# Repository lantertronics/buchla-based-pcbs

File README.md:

# buchla-based-pcbs

291

294

295

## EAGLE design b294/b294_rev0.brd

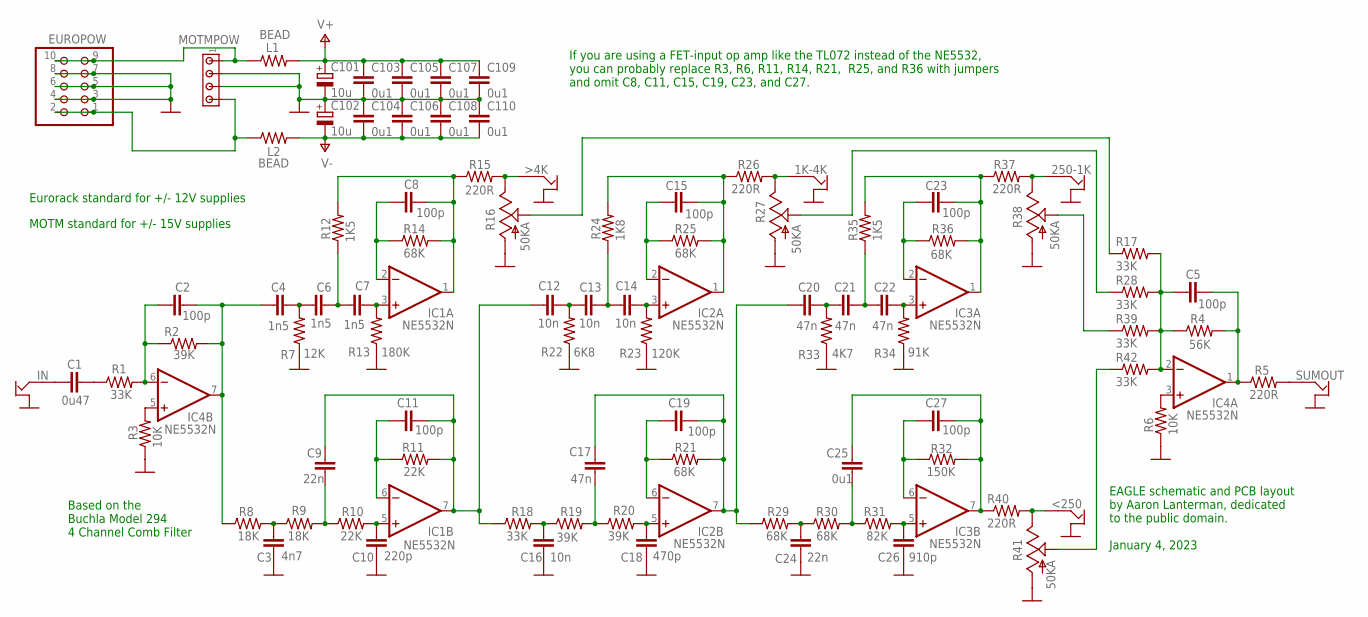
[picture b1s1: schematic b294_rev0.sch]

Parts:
1K-4K, 250-1K: OFFBOARD2JACKALT_AARON; OFFBOARD2JACKALT
<250: OFFBOARD2JACKALT_AARON; OFFBOARD2JACKALT
>4K: OFFBOARD2JACKALT_AARON; OFFBOARD2JACKALT
C1: 0u47; C050-025X075
C2, C5, C8, C11, C15, C19, C23, C27: 100p; C050-025X075
C3: 4n7; C050-025X075
C4, C6, C7: 1n5; C050-025X075
C9, C24: 22n; C050-025X075
C10: 220p; C050-025X075
C12, C13, C14, C16: 10n; C050-025X075
C17, C20, C21, C22: 47n; C050-025X075
C18: 470p; C050-025X075
C25, C103, C104, C105, C106, C107, C108, C109, C110: 0u1; C050-025X075
C26: 910p; C050-025X075
C101, C102: 10u; E1,8-4
EUROPOW: PINHD-2X5; 2X05
IC1, IC2, IC3, IC4: NE5532N; DIL08
IN: OFFBOARD2JACKALT_AARON; OFFBOARD2JACKALT
L1, L2: BEAD; 0207/10
MOTMPOW: MTA04-156; 1X4MTA
R1, R17, R18, R28, R39, R42: 33K; 0207/10
R2, R19, R20: 39K; 0207/10
R3, R6: 10K; 0207/10
R4: 56K; 0207/10
R5, R15, R26, R37, R40: 220R; 0207/10
R7: 12K; 0207/10
R8, R9: 18K; 0207/10
R10, R11: 22K; 0207/10
R12, R35: 1K5; 0207/10
R13: 180K; 0207/10
R14, R21, R25, R29, R30, R36: 68K; 0207/10
R16, R27, R38, R41: 50KA; B64Y
R22: 6K8; 0207/10
R23: 120K; 0207/10
R24: 1K8; 0207/10
R31: 82K; 0207/10
R32: 150K; 0207/10
R33: 4K7; 0207/10
R34: 91K; 0207/10
SUMOUT: OFFBOARD2JACKALT_AARON; OFFBOARD2JACKALT

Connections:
GND: 1K-4K.GND, 250-1K.GND, <250.GND, >4K.GND, C3.2, C10.2, C16.2, C18.2, C24.2, C26.2, C101.-, C102.+, C103.2, C104.1, C105.2, C106.1, C107.2, C108.1, C109.2, C110.1, EUROPOW.3, EUROPOW.4, EUROPOW.5, EUROPOW.6, EUROPOW.7, EUROPOW.8, IN.GND, MOTMPOW.2, MOTMPOW.3, R3.1, R6.1, R7.1, R13.1, R16.A, R22.1, R23.1, R27.A, R33.1, R34.1, R38.A, R41.A, SUMOUT.GND
unnamed: C18.1, IC2.5 (+IN), R20.2
unnamed: C17.2, R19.2, R20.1
unnamed: C16.1, R18.2, R19.1
unnamed: C26.1, IC3.5 (+IN), R31.2
unnamed: C25.2, R30.2, R31.1
unnamed: C24.1, R29.2, R30.1
unnamed: C10.1, IC1.5 (+IN), R10.2
unnamed: >4K.SIGNAL, R15.2, R16.E
unnamed: C3.1, R8.2, R9.1
unnamed: C11.1, IC1.6 (-IN), R11.1
unnamed: C9.1, C11.2, C12.1, IC1.7 (OUT), R11.2, R18.1
unnamed: C19.1, IC2.6 (-IN), R21.1
unnamed: C17.1, C19.2, C20.1, IC2.7 (OUT), R21.2, R29.1
unnamed: C2.2, C4.1, IC4.7 (OUT), R2.2, R8.1
unnamed: C25.1, C27.2, IC3.7 (OUT), R32.2, R40.1
unnamed: C2.1, IC4.6 (-IN), R1.2, R2.1
unnamed: C8.1, IC1.2 (-IN), R14.1
unnamed: C1.1, IN.SIGNAL
unnamed: C15.1, IC2.2 (-IN), R25.1
unnamed: C15.2, IC2.1 (OUT), R24.2, R25.2, R26.1
unnamed: C23.1, IC3.2 (-IN), R36.1
unnamed: C23.2, IC3.1 (OUT), R35.2, R36.2, R37.1
unnamed: 1K-4K.SIGNAL, R26.2, R27.E
unnamed: C9.2, R9.2, R10.1
unnamed: 250-1K.SIGNAL, R37.2, R38.E
unnamed: C7.2, IC1.3 (+IN), R13.2
unnamed: C27.1, IC3.6 (-IN), R32.1
unnamed: C6.2, C7.1, R12.1
unnamed: C4.2, C6.1, R7.2
unnamed: C14.2, IC2.3 (+IN), R23.2
unnamed: C13.2, C14.1, R24.1
unnamed: C12.2, C13.1, R22.2
unnamed: C22.2, IC3.3 (+IN), R34.2
unnamed: C21.2, C22.1, R35.1
unnamed: C20.2, C21.1, R33.2
unnamed: <250.SIGNAL, R40.2, R41.E
unnamed: C5.1, IC4.2 (-IN), R4.1, R17.2, R28.2, R39.2, R42.2
unnamed: R38.S, R39.1
unnamed: R27.S, R28.1
unnamed: R16.S, R17.1
unnamed: R41.S, R42.1
unnamed: C5.2, IC4.1 (OUT), R4.2, R5.1
unnamed: R5.2, SUMOUT.SIGNAL
unnamed: IC4.3 (+IN), R6.2
unnamed: IC4.5 (+IN), R3.2
unnamed: C1.2, R1.1
unnamed: EUROPOW.1, EUROPOW.2, L2.1, MOTMPOW.4
unnamed: EUROPOW.9, EUROPOW.10, L1.1, MOTMPOW.1
P1: C8.2, IC1.1 (OUT), R12.2, R14.2, R15.1
V+: C101.+, C103.1, C105.1, C107.1, C109.1, IC1.8 (V+), IC2.8 (V+), IC3.8 (V+), IC4.8 (V+), L1.2
V-: C102.-, C104.2, C106.2, C108.2, C110.2, IC1.4 (V-), IC2.4 (V-), IC3.4 (V-), IC4.4 (V-), L2.2

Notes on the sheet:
Eurorack standard for +/- 12V supplies
MOTM standard for +/- 15V supplies
EAGLE schematic and PCB layout by Aaron Lanterman, dedicated to the public domain. January 4, 2023
If you are using a FET-input op amp like the TL072 instead of the NE5532, you can probably replace R3, R6, R11, R14, R21, R25, and R36 with jumpers and omit C8, C11, C15, C19, C23, and C27.
Based on the Buchla Model 294 4 Channel Comb Filter

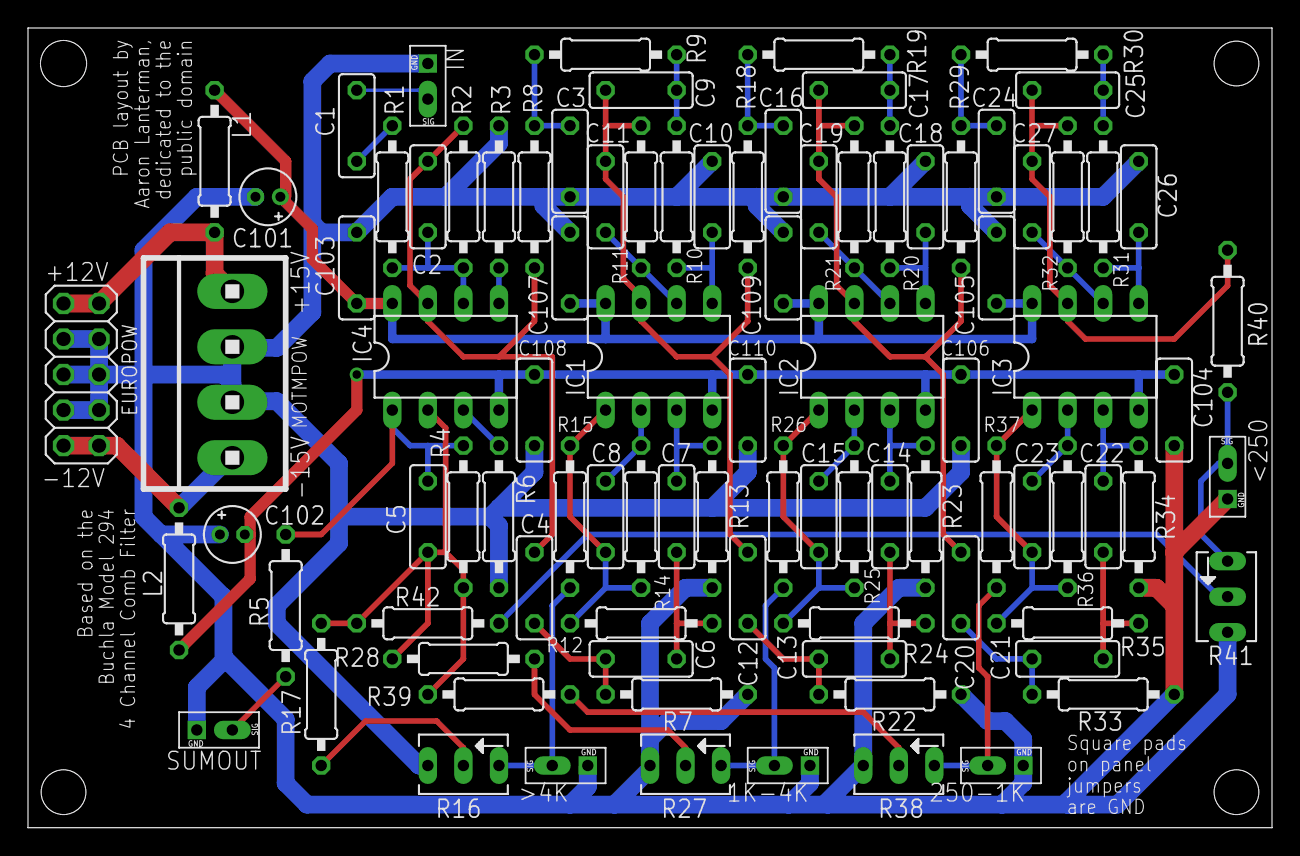
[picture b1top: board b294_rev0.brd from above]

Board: 2 copper layers, 88.9 x 57.1 mm, 93 parts (0 on the bottom side), 52 nets.

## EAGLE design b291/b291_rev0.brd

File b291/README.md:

Revision 0 has an error on the silkscreen: the labels for C6 and C102 are swapped (just the "C6" and "C102" markings; the 0.1 uF and 470 pF labels inside the capacitor boxea are correct).

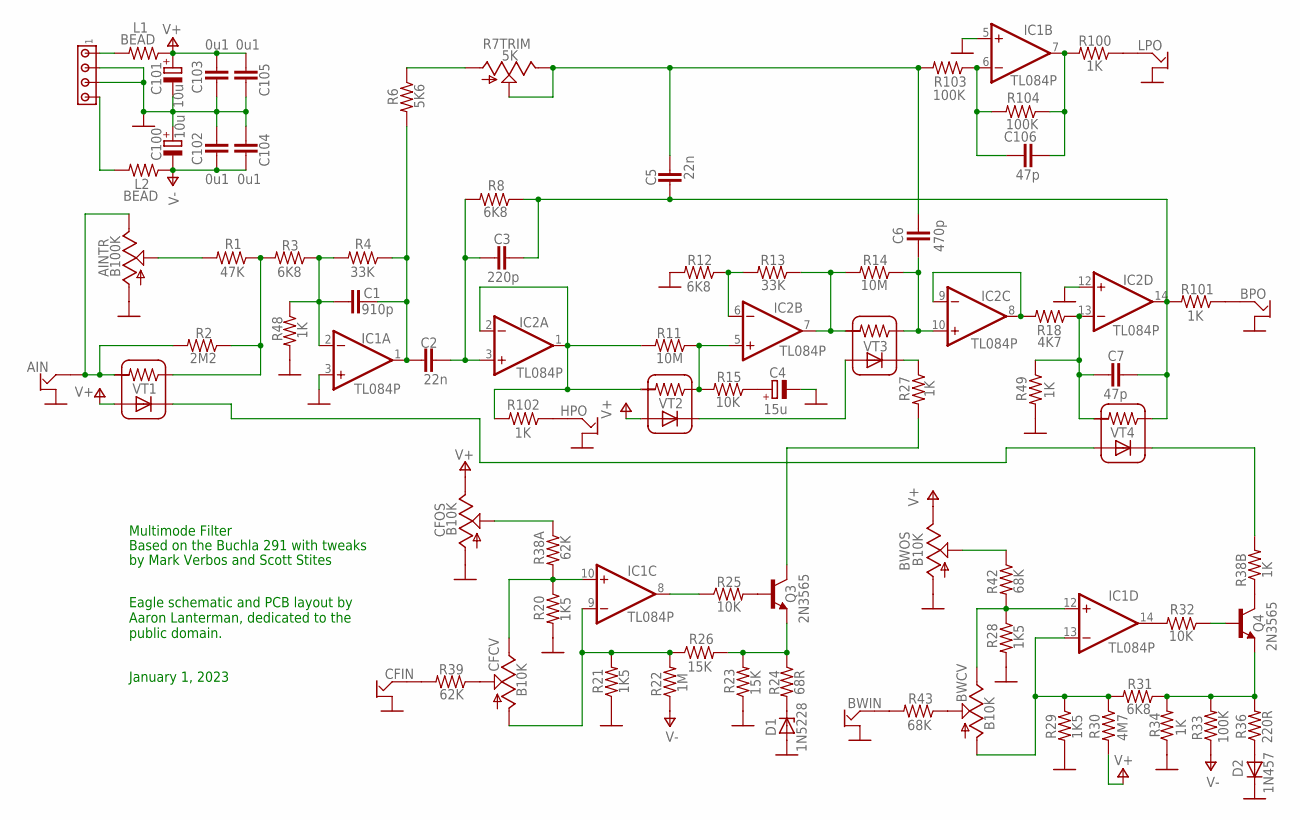
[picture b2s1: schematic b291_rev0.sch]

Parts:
AIN: OFFBOARD2JACK
AINTR: B100K; B64Y
BPO: OFFBOARD2JACK
BWCV: B10K; B64Y
BWIN: OFFBOARD2JACK
BWOS: B10K; B64Y
C1: 910p; C050-025X075
C2, C5: 22n; C050-025X075
C3: 220p; C050-025X075
C4: 15u; E1,8-4
C6: 470p; C050-025X075
C7, C106: 47p; C050-025X075
C100, C101: 10u; E1,8-4
C102, C103, C104, C105: 0u1; C050-025X075
CFCV: B10K; B64Y
CFIN: OFFBOARD2JACK
CFOS: B10K; B64Y
D1: 1N5228; DO35Z10
D2: 1N457; DO35-7
HPO: OFFBOARD2JACK
IC1, IC2: TL084P; DIL14
J1: MTA04-156; 1X4MTA
L1, L2: BEAD; 0309/10
LPO: OFFBOARD2JACK
Q3, Q4: 2N3565; TO92
R1: 47K; 0207/10
R2: 2M2; 0207/10
R3, R8, R12, R31: 6K8; 0207/10
R4, R13: 33K; 0207/10
R6: 5K6; 0207/10
R7TRIM: 5K; B64Y
R11, R14: 10M; 0207/10
R15, R25, R32: 10K; 0207/10
R18: 4K7; 0207/10
R20, R21, R28, R29: 1K5; 0207/10
R22: 1M; 0207/10
R23, R26: 15K; 0207/10
R24: 68R; 0207/10
R27, R34, R38B, R48, R49, R100, R101, R102: 1K; 0207/10
R30: 4M7; 0207/10
R33, R103, R104: 100K; 0207/10
R36: 220R; 0207/10
R38A, R39: 62K; 0207/10
R42, R43: 68K; 0207/10
VT1, VT2, VT3, VT4: VACTROLSINGLE

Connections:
GND: AIN.GND, AINTR.A, BPO.GND, BWIN.GND, BWOS.A, C4.-, C100.+, C101.-, C102.1, C103.2, C104.1, C105.2, CFIN.GND, CFOS.A, D1.A, D2.C, HPO.GND, IC1.3 (+IN), IC1.5 (+IN), IC2.12 (+IN), J1.2, J1.3, LPO.GND, R12.2, R20.2, R21.1, R23.1, R28.2, R29.2, R34.1, R48.2, R49.2
unnamed: R27.1, VT3.LED-
unnamed: IC2.8 (OUT), IC2.9 (-IN), R18.2
unnamed: C6.1, IC2.10 (+IN), R14.1, VT3.CELLA (RA)
unnamed: IC2.7 (OUT), R13.1, R14.2, VT3.CELLB (RB)
unnamed: IC2.6 (-IN), R12.1, R13.2
unnamed: IC2.5 (+IN), R11.1, R15.2, VT2.CELLA (RA)
unnamed: IC2.1 (OUT), IC2.2 (-IN), R11.2, R102.2, VT2.CELLB (RB)
unnamed: VT2.LED-, VT3.LED+
unnamed: Q3.1 (C), R27.2
unnamed: C2.2, C3.1, IC2.3 (+IN), R8.2
unnamed: C5.2, C6.2, R7TRIM.E, R7TRIM.S, R103.2
unnamed: C3.2, C5.1, C7.2, IC2.14 (OUT), R8.1, R101.2, VT4.CELLA (RA)
unnamed: C1.2, C2.1, IC1.1 (OUT), R4.1, R6.2
unnamed: R6.1, R7TRIM.A
unnamed: C1.1, IC1.2 (-IN), R3.1, R4.2, R48.1
unnamed: R38B.2, VT4.LED-
unnamed: BPO.SIGNAL, R101.1
unnamed: Q3.2 (B), R25.2
unnamed: C7.1, IC2.13 (-IN), R18.1, R49.1, VT4.CELLB (RB)
unnamed: Q3.3 (E), R23.2, R24.1, R26.2
unnamed: CFCV.A, IC1.9 (-IN), R21.2, R22.2, R26.1
unnamed: Q4.1 (C), R38B.1
unnamed: Q4.2 (B), R32.1
unnamed: Q4.3 (E), R31.1, R33.2, R34.2, R36.2
unnamed: BWCV.A, IC1.13 (-IN), R29.1, R30.1, R31.2
unnamed: IC1.8 (OUT), R25.1
unnamed: IC1.14 (OUT), R32.2
unnamed: CFCV.E, IC1.10 (+IN), R20.1, R38A.2
unnamed: BWCV.E, IC1.12 (+IN), R28.1, R42.2
unnamed: CFOS.S, R38A.1
unnamed: BWOS.S, R42.1
unnamed: AIN.SIGNAL, AINTR.E, R2.2, VT1.CELLB (RB)
unnamed: J1.1, L1.2
unnamed: VT1.LED-, VT4.LED+
unnamed: AINTR.S, R1.2
unnamed: D1.C, R24.2
unnamed: BWIN.SIGNAL, R43.2
unnamed: BWCV.S, R43.1
unnamed: CFCV.S, R39.1
unnamed: CFIN.SIGNAL, R39.2
unnamed: D2.A, R36.1
unnamed: C106.1, IC1.6 (-IN), R103.1, R104.2
unnamed: C106.2, IC1.7 (OUT), R100.2, R104.1
unnamed: R1.1, R2.1, R3.2, VT1.CELLA (RA)
unnamed: LPO.SIGNAL, R100.1
unnamed: HPO.SIGNAL, R102.1
unnamed: C4.+, R15.1
unnamed: J1.4, L2.2
V+: BWOS.E, C101.+, C103.1, C105.1, CFOS.E, IC1.4 (V+), IC2.4 (V+), L1.1, R30.2, VT1.LED+, VT2.LED+
V-: C100.-, C102.2, C104.2, IC1.11 (V-), IC2.11 (V-), L2.1, R22.1, R33.1

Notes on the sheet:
Multimode Filter
Based on the Buchla 291 with tweaks
Eagle schematic and PCB layout by Aaron Lanterman, dedicated to the public domain.
by Mark Verbos and Scott Stites
January 1, 2023

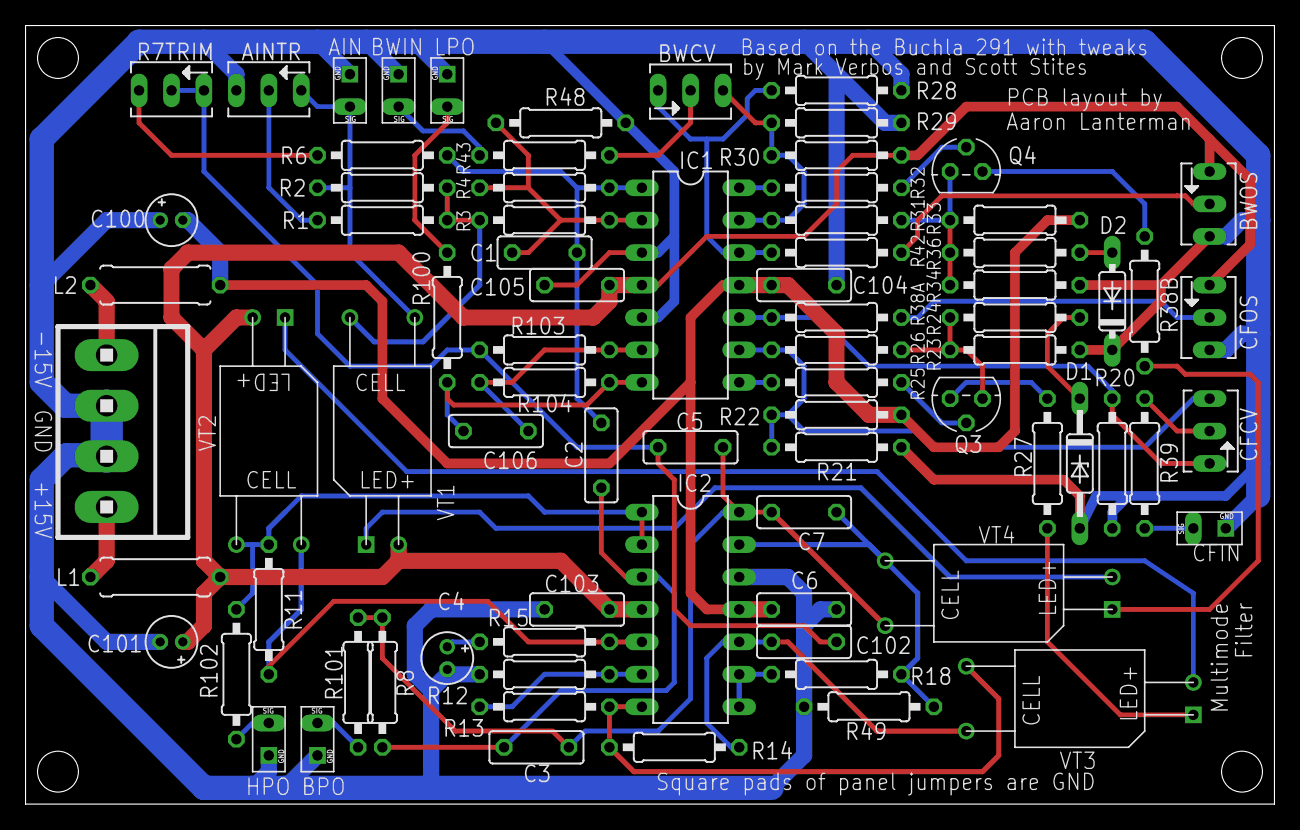
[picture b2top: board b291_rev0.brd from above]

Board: 2 copper layers, 97.8 x 61.0 mm, 79 parts (0 on the bottom side), 51 nets.

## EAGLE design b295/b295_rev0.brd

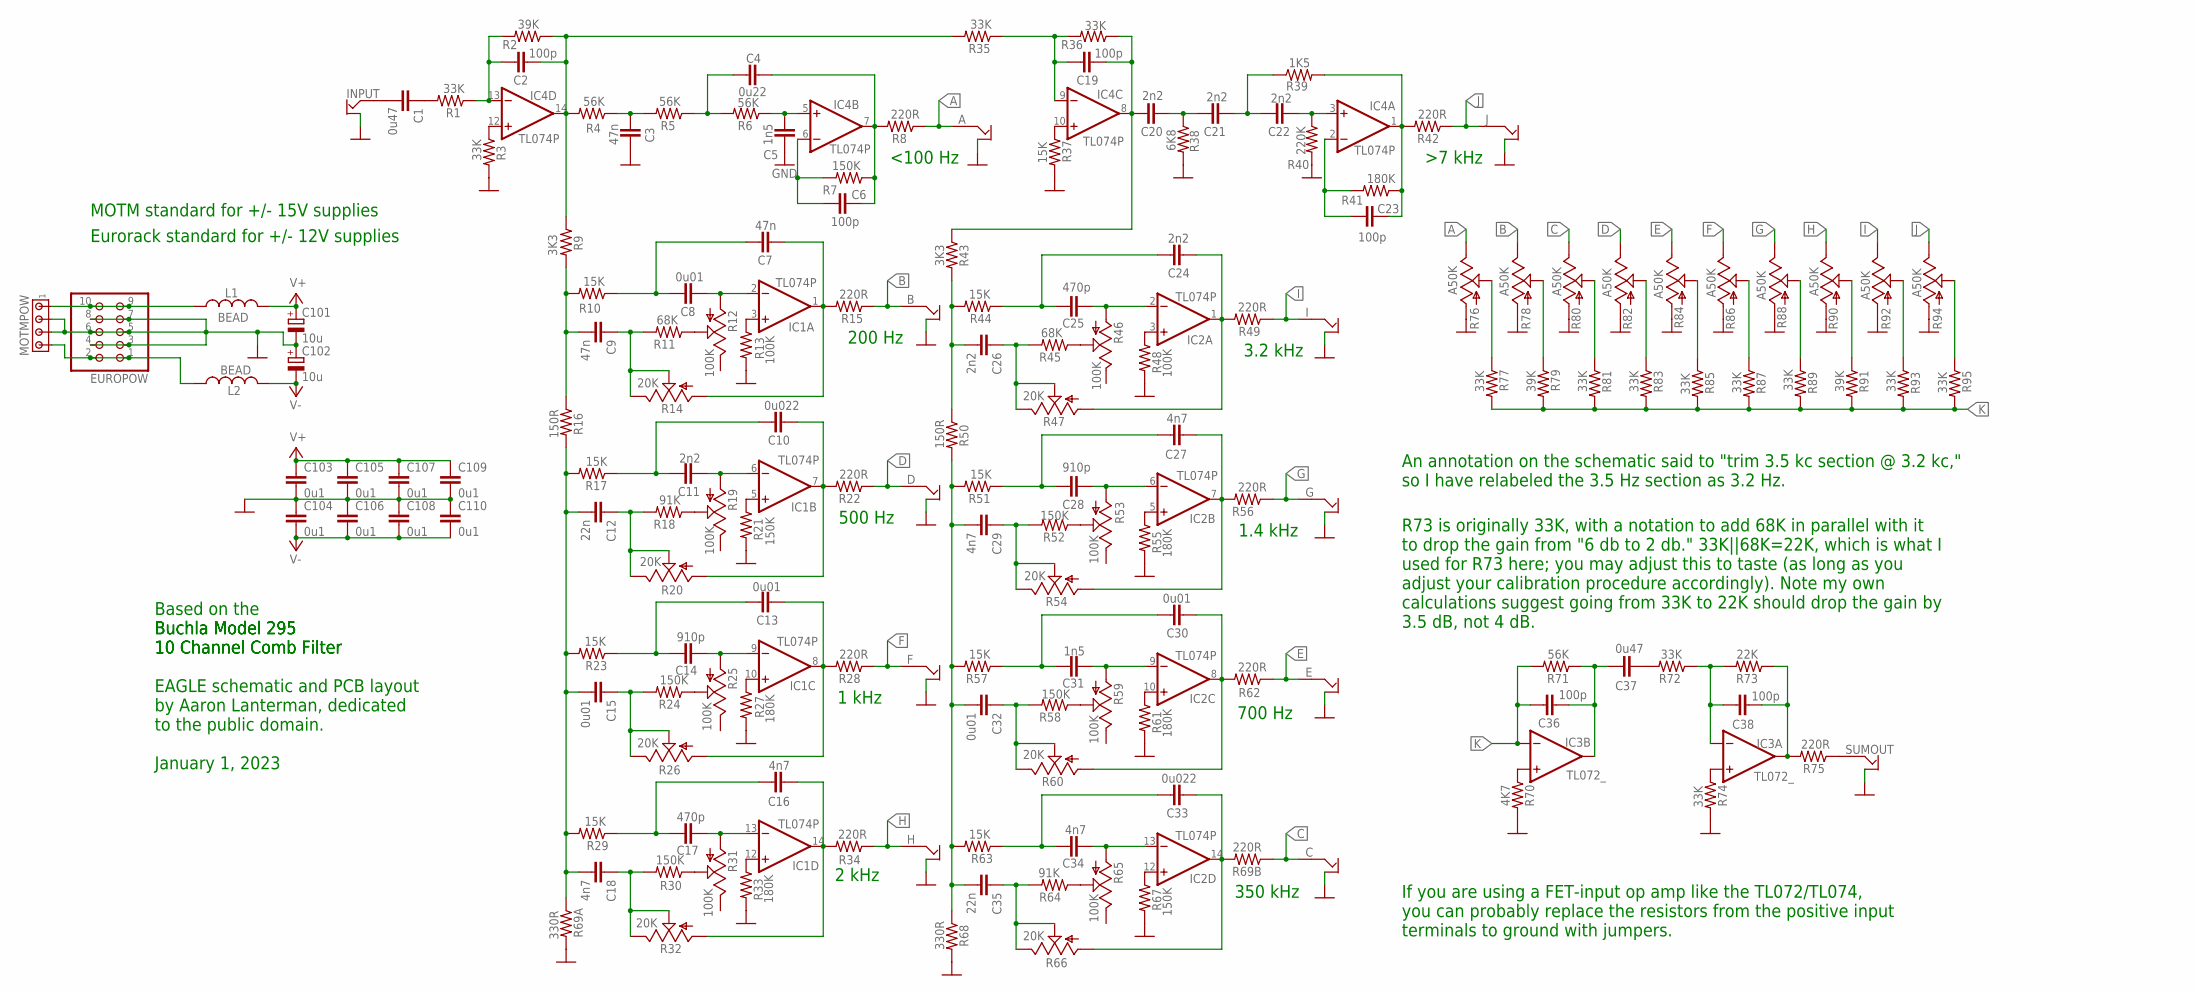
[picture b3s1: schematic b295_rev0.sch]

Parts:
A: OFFBOARD2JACKALT_AARON; OFFBOARD2JACKALT
B: OFFBOARD2JACKALT_AARON; OFFBOARD2JACKALT
C: OFFBOARD2JACKALT_AARON; OFFBOARD2JACKALT
C1, C37: 0u47; C050-025X075-AARON
C2, C6, C19, C23, C36, C38: 100p; C050-025X075-AARON
C3, C7, C9: 47n; C050-025X075-AARON
C4: 0u22; C050-025X075-AARON
C5, C31: 1n5; C050-025X075-AARON
C8, C13, C15, C30, C32: 0u01; C050-025X075-AARON
C10, C33: 0u022; C050-025X075-AARON
C11, C20, C21, C22, C24, C26: 2n2; C050-025X075-AARON
C12, C35: 22n; C050-025X075-AARON
C14, C28: 910p; C050-025X075-AARON
C16, C18, C27, C29, C34: 4n7; C050-025X075-AARON
C17, C25: 470p; C050-025X075-AARON
C101, C102: 10u; E1,8-4
C103, C104, C105, C106, C107, C108, C109, C110: 0u1; C050-025X075-AARON
D: OFFBOARD2JACKALT_AARON; OFFBOARD2JACKALT
E: OFFBOARD2JACKALT_AARON; OFFBOARD2JACKALT
EUROPOW: PINHD-2X5; 2X05
F: OFFBOARD2JACKALT_AARON; OFFBOARD2JACKALT
G: OFFBOARD2JACKALT_AARON; OFFBOARD2JACKALT
H: OFFBOARD2JACKALT_AARON; OFFBOARD2JACKALT
I: OFFBOARD2JACKALT_AARON; OFFBOARD2JACKALT
IC1, IC2, IC4: TL074P; DIL14
IC3: TL072_; DIL08
INPUT: OFFBOARD2JACKALT_AARON; OFFBOARD2JACKALT
J: OFFBOARD2JACKALT_AARON; OFFBOARD2JACKALT
L1, L2: BEAD; 0207/10
MOTMPOW: MTA04-156; 1X4MTA
R1, R3, R35, R36, R72, R74, R77, R81, R83, R85, R87, R89, R93, R95: 33K; 0207/10
R2, R79, R91: 39K; 0207/10
R4, R5, R6, R71: 56K; 0207/10
R7, R21, R24, R30, R52, R58, R67: 150K; 0207/10
R8, R15, R22, R28, R34, R42, R49, R56, R62, R69B, R75: 220R; 0207/10
R9, R43: 3K3; 0207/10
R10, R17, R23, R29, R37, R44, R51, R57, R63: 15K; 0207/10
R11, R45: 68K; 0207/10
R12, R19, R25, R31, R46, R53, R59, R65: 100K; B64Y
R13, R48: 100K; 0207/10
R14, R20, R26, R32, R47, R54, R60, R66: 20K; B64Y
R16, R50: 150R; 0207/10
R18, R64: 91K; 0207/10
R27, R33, R41, R55, R61: 180K; 0207/10
R38: 6K8; 0207/10
R39: 1K5; 0207/10
R40: 220K; 0207/10
R68, R69A: 330R; 0207/10
R70: 4K7; 0207/10
R73: 22K; 0207/10
R76, R78, R80, R82, R84, R86, R88, R90, R92, R94: A50K; B64Y
SUMOUT: OFFBOARD2JACKALT_AARON; OFFBOARD2JACKALT

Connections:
A: A.SIGNAL, R8.1, R76.E
B: B.SIGNAL, R15.1, R78.E
C: C.SIGNAL, R69B.1, R80.E
C18A: C18.1, R30.2, R32.E, R32.S
C32A: C32.1, R58.2, R60.E, R60.S
D: D.SIGNAL, R22.1, R82.E
E: E.SIGNAL, R62.1, R84.E
F: F.SIGNAL, R28.1, R86.E
G: G.SIGNAL, R56.1, R88.E
GND: A.GND, B.GND, C.GND, C3.1, C5.1, C101.-, C102.+, C103.2, C104.1, C105.2, C106.1, C107.2, C108.1, C109.2, C110.1, D.GND, E.GND, EUROPOW.3, EUROPOW.4, EUROPOW.5, EUROPOW.6, EUROPOW.7, EUROPOW.8, F.GND, G.GND, H.GND, I.GND, INPUT.GND, J.GND, MOTMPOW.2, MOTMPOW.3, R3.2, R13.2, R21.2, R27.2, R33.2, R37.2, R38.2, R40.2, R48.2, R55.2, R61.2, R67.2, R68.2, R69A.2, R70.2, R74.2, R76.A, R78.A, R80.A, R82.A, R84.A, R86.A, R88.A, R90.A, R92.A, R94.A, SUMOUT.GND
H: H.SIGNAL, R34.1, R90.E
I: I.SIGNAL, R49.1, R92.E
J: J.SIGNAL, R42.1, R94.E
K: C36.2, IC3.6 (-IN), R71.2, R77.2, R79.2, R81.2, R83.2, R85.2, R87.2, R89.2, R91.2, R93.2, R95.2
unnamed: C13.1, IC1.8 (OUT), R26.A, R28.2
unnamed: C16.1, IC1.14 (OUT), R32.A, R34.2
unnamed: C30.1, IC2.8 (OUT), R60.A, R62.2
unnamed: C33.1, IC2.14 (OUT), R66.A, R69B.2
unnamed: C14.1, IC1.9 (-IN), R25.A
unnamed: C17.1, IC1.13 (-IN), R31.A
unnamed: C16.2, C17.2, R29.1
unnamed: C30.2, C31.2, R57.1
unnamed: R24.1, R25.S
unnamed: C33.2, C34.2, R63.1
unnamed: R30.1, R31.S
unnamed: R64.1, R65.S
unnamed: R92.S, R93.1
unnamed: R94.S, R95.1
unnamed: C37.1, R72.2
unnamed: IC1.3 (+IN), R13.1
unnamed: C13.2, C14.2, R23.1
unnamed: C31.1, IC2.9 (-IN), R59.A
unnamed: C34.1, IC2.13 (-IN), R65.A
unnamed: R58.1, R59.S
unnamed: C15.1, R24.2, R26.E, R26.S
unnamed: C38.2, IC3.2 (-IN), R72.1, R73.2
unnamed: C35.1, R64.2, R66.E, R66.S
unnamed: C36.1, C37.2, IC3.7 (OUT), R71.1
unnamed: IC1.5 (+IN), R21.1
unnamed: C12.2, C15.2, C18.2, R16.2, R17.2, R23.2, R29.2, R69A.1
unnamed: IC1.10 (+IN), R27.1
unnamed: C29.2, C32.2, C35.2, R50.2, R51.2, R57.2, R63.2, R68.1
unnamed: C7.1, IC1.1 (OUT), R14.A, R15.2
unnamed: C10.1, IC1.7 (OUT), R20.A, R22.2
unnamed: IC1.12 (+IN), R33.1
unnamed: IC2.12 (+IN), R67.1
unnamed: C24.1, IC2.1 (OUT), R47.A, R49.2
unnamed: C27.1, IC2.7 (OUT), R54.A, R56.2
unnamed: C8.1, IC1.2 (-IN), R12.A
unnamed: C10.2, C11.2, R17.1
unnamed: C24.2, C25.2, R44.1
unnamed: C27.2, C28.2, R51.1
unnamed: C38.1, IC3.1 (OUT), R73.1, R75.2
unnamed: R75.1, SUMOUT.SIGNAL
unnamed: R76.S, R77.1
unnamed: R78.S, R79.1
unnamed: C7.2, C8.2, R10.1
unnamed: C25.1, IC2.2 (-IN), R46.A
unnamed: C28.1, IC2.6 (-IN), R53.A
unnamed: C11.1, IC1.6 (-IN), R19.A
unnamed: R11.1, R12.S
unnamed: R18.1, R19.S
unnamed: R52.1, R53.S
unnamed: R45.1, R46.S
unnamed: C9.1, R11.2, R14.E, R14.S
unnamed: C12.1, R18.2, R20.E, R20.S
unnamed: C29.1, R52.2, R54.E, R54.S
unnamed: C26.1, R45.2, R47.E, R47.S
unnamed: C9.2, R9.2, R10.2, R16.1
unnamed: IC2.10 (+IN), R61.1
unnamed: C26.2, R43.2, R44.2, R50.1
unnamed: IC2.5 (+IN), R55.1
unnamed: R80.S, R81.1
unnamed: R82.S, R83.1
unnamed: R84.S, R85.1
unnamed: EUROPOW.9, EUROPOW.10, L1.1, MOTMPOW.1
unnamed: EUROPOW.1, EUROPOW.2, L2.1, MOTMPOW.4
unnamed: R86.S, R87.1
unnamed: R88.S, R89.1
unnamed: R90.S, R91.1
unnamed: C3.2, R4.1, R5.2
unnamed: C4.2, R5.1, R6.2
unnamed: C4.1, C6.1, IC4.7 (OUT), R7.1, R8.2
unnamed: C5.2, IC4.5 (+IN), R6.1
unnamed: C6.2, IC4.6 (-IN), R7.2
unnamed: C2.1, IC4.14 (OUT), R2.1, R4.2, R9.1, R35.2
unnamed: C2.2, IC4.13 (-IN), R1.1, R2.2
unnamed: IC4.12 (+IN), R3.1
unnamed: C1.1, R1.2
unnamed: C1.2, INPUT.SIGNAL
unnamed: C19.2, IC4.9 (-IN), R35.1, R36.2
unnamed: C19.1, C20.2, IC4.8 (OUT), R36.1, R43.1
unnamed: C20.1, C21.2, R38.1
unnamed: C21.1, C22.2, R39.1
unnamed: C22.1, IC4.3 (+IN), R40.1
unnamed: C23.2, IC4.2 (-IN), R41.2
unnamed: C23.1, IC4.1 (OUT), R39.2, R41.1, R42.2
unnamed: IC2.3 (+IN), R48.1
unnamed: IC4.10 (+IN), R37.1
unnamed: IC3.5 (+IN), R70.1
unnamed: IC3.3 (+IN), R74.1
V+: C101.+, C103.1, C105.1, C107.1, C109.1, IC1.4 (V+), IC2.4 (V+), IC3.8 (V+), IC4.4 (V+), L1.2
V-: C102.-, C104.2, C106.2, C108.2, C110.2, IC1.11 (V-), IC2.11 (V-), IC3.4 (V-), IC4.11 (V-), L2.2

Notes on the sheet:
MOTM standard for +/- 15V supplies
Eurorack standard for +/- 12V supplies
EAGLE schematic and PCB layout by Aaron Lanterman, dedicated to the public domain. January 1, 2023
R73 is originally 33K, with a notation to add 68K in parallel with it to drop the gain from "6 db to 2 db." 33K||68K=22K, which is what I used for R73 here; you may adjust this to taste (as long as you adjust your calibration procedure accordingly). Note my own calculations suggest going from 33K t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
An annotation on the schematic said to "trim 3.5 kc section @ 3.2 kc," so I have relabeled the 3.5 Hz section as 3.2 Hz.
If you are using a FET-input op amp like the TL072/TL074, you can probably replace the resistors from the positive input terminals to ground with jumpers.
1 kHz
<100 Hz
200 Hz
3.2 kHz
500 Hz
1.4 kHz
700 Hz
350 kHz
2 kHz
Buchla Model 295 10 Channel Comb Filter
Based on the Buchla Model 295 10 Channel Comb Filter

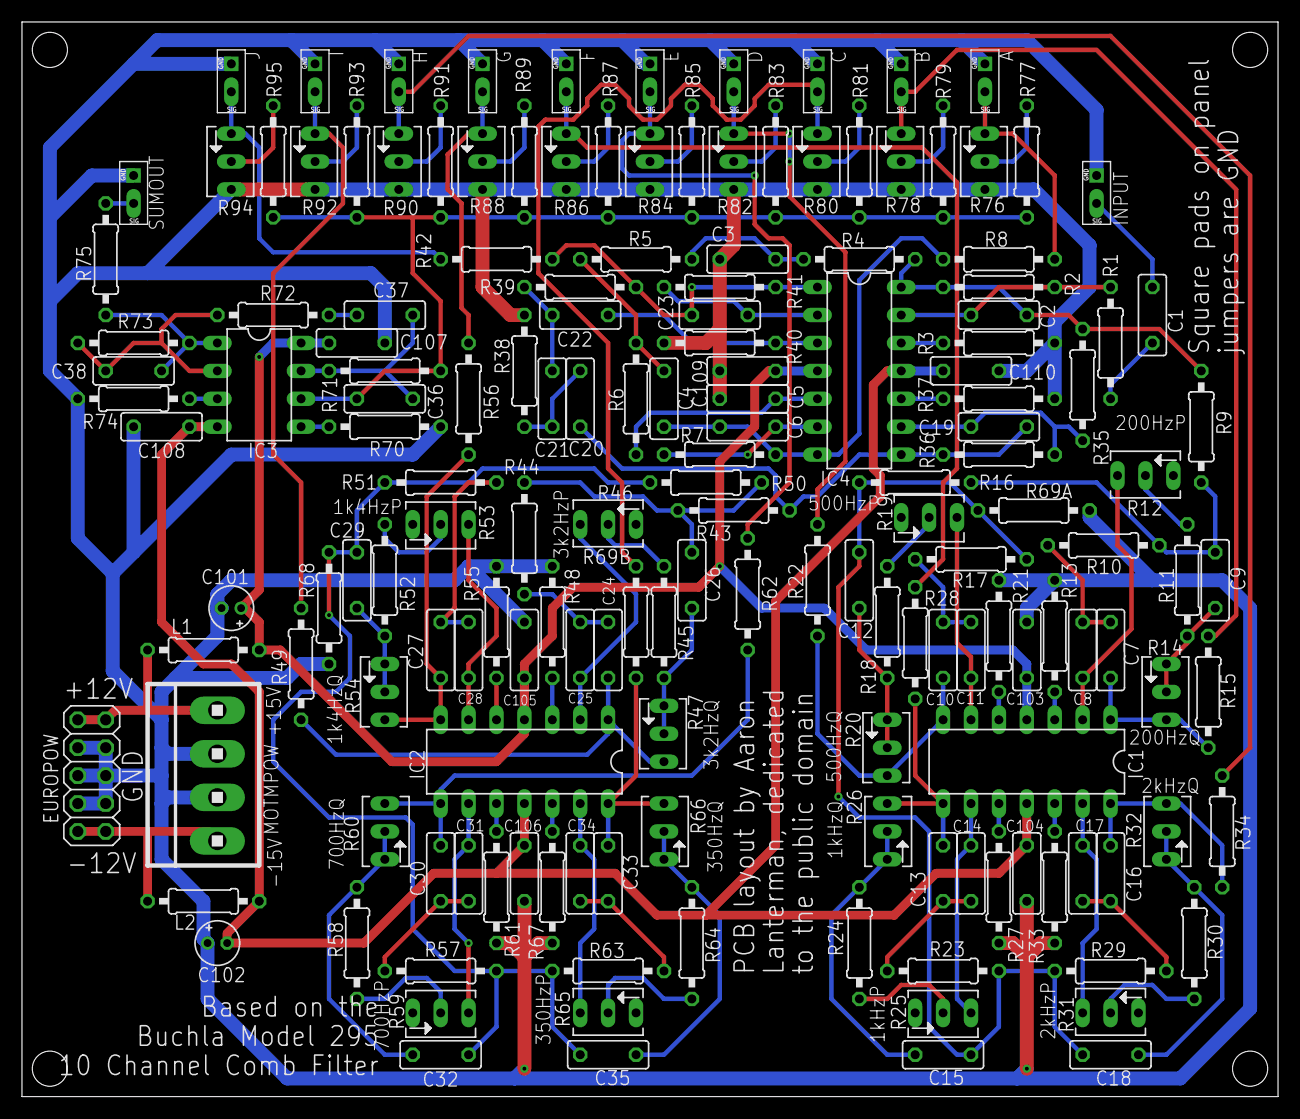
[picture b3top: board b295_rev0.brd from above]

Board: 2 copper layers, 114.3 x 97.8 mm, 164 parts (0 on the bottom side), 103 nets.

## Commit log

2023-01-08 Create music-easel-adaptations
2023-01-08 Create mea-timbre-crossfade
2023-01-08 Rename mea-timbre-crossfade to mea-timbre-crossfade-readme
2023-01-08 Create dummy
2023-01-08 Rename music-easel-adaptations/mea-timbre-crossfade-readme to music-easel-adaptations/mea-timbre-crossfader/README.md
